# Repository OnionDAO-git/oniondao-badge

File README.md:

# OnionDAO Badge

An open-source, hacker-conference-style electronic badge built around the
**ESP32-S3-WROOM-1-N8R8** (8 MB flash + 8 MB Octal PSRAM), with swappable
RF / audio / storage modules, an e-paper
(or TFT) display socket, a secure element, an I²C IO expander for the button
matrix, and dual side-mounted expansion ports for hardware mods.

Designed in **KiCad 9.0.3**. The hardware (schematics, PCB, BOM, fabrication
outputs, STEP model) lives in [`pcb/`](pcb). The software lives in
[`software/`](software) and is community-driven — PRs welcome.

> **🧅 Just got a badge?** New attendees start with the
> **[Badge Quickstart](docs/BADGE-QUICKSTART.md)** — power it on, confirm Onion
> OS is running, and link it to your profile in ~5 minutes.

---

## Table of Contents

- [At a Glance](#at-a-glance)
- [Block Diagram](#block-diagram)
- [Repository Layout](#repository-layout)
- [Hardware Documentation](#hardware-documentation)
- [Quick Start (Software)](#quick-start-software)
- [Pinout Cheat Sheet](#pinout-cheat-sheet)
- [Contributing Software Mods & Guides](#contributing-software-mods--guides)
- [License](#license)

---

## At a Glance

| | |
|---|---|
| **MCU** | Espressif **ESP32-S3-WROOM-1-N8R8** (Wi-Fi + BT 5.0 LE, dual-core Xtensa LX7) |
| **Memory** | 8 MB quad-SPI flash (`N8`) + 8 MB **Octal-SPI (OPI)** PSRAM (`R8`) |
| **USB / Serial** | WCH **CH340C** USB-UART bridge w/ DTR/RTS auto-reset |
| **Secure Element** | Microchip **ATECC608B-SSHDA** (I²C, power-gated) |
| **IO Expander** | TI **TCA9534** (I²C, addr `0x20`) driving the 6-button matrix (PB1–PB6) |
| **Display** | 24-pin socket (`J4`) — E-Ink / TFT SPI with `BUSY`, `RST`, `DC`, `CS`, `SCK`, `MOSI` |
| **Audio (mod)** | NS4168 I²S amplifier + SPH0641 PDM mic (Sound Module) |
| **Sub-GHz (mod)** | TI **CC1101** SPI radio (315/433/868/915 MHz) |
| **Expansion** | Left port `J8` (10 pin) + Right port `J10` (10 pin) — VCC / GND + GPIO |
| **GPIO Used** | 28 of the available ESP32-S3 GPIOs |
| **Power Gate** | Q5 (SS8050) on `GPIO18` enables the peripheral `PWR` rail |

## Block Diagram

```
                              ┌────────────────────────┐
        USB-C ── CH340C ──────│ UART0  GPIO43/44       │
                              │                        │
   ┌── BOOT btn ── GPIO0 ─────│ STRAP                  │
   │                          │                        │
   │   ATECC608B ──┬─ SCL G9 ─│ I²C0                   │
   │   TCA9534  ──┘  SDA G10  │   ◄── INT G1 (PBINT)   │
   │                          │                        │
   │   J4 Display ─SPI──── G11/12/13/14/17/21          │
   │                          │                        │
   │   J8 Left   ── G48/47/19/42/41/40                  │  ESP32-S3-WROOM-1
   │   J10 Right ── G38/39/16/15/7/6/5/4                │
   │                          │                        │
   │   GPIO18 ──── Q5 ────────│ PWR rail to gated peripherals
   │   GPIO8  ──── SE_EN  ────│ ATECC608B power gate
   │                          └────────────────────────┘
   │
   └── PB1..PB6 ── TCA9534 P0..P5 ──► INT line ── GPIO1
```

## Repository Layout

```
oniondao-badge/
├── README.md                   ← you are here
├── pcb/                        ← KiCad 9.0.3 hardware sources
│   ├── oniondao-badge.kicad_pro
│   ├── oniondao-badge.kicad_sch         (top-level schematic)
│   ├── oniondao-badge.kicad_pcb         (board layout)
│   ├── CC1101_MOD.kicad_sch              (Sub-GHz RF module)
│   ├── SOUND_MOD.kicad_sch               (I²S amp + PDM mic)
│   ├── oniondao-badge.step              (full 3D model)
│   ├── 3d/                               (additional STEP assets)
│   ├── production/                       (gerbers, BOMs, netlist)
│   ├── oniondao-badge_top.png           (board render — top)
│   ├── oniondao-badge_btm.png           (board render — bottom)
│   └── oniondao badge.html                   (interactive IO reference)
├── docs/
│   ├── HARDWARE.md             ← deep dive on every subsystem
│   ├── PINOUT.md               ← full GPIO ↔ net ↔ peripheral table
│   ├── MODULES.md              ← swappable modules & their pinmaps
│   └── CONTRIBUTING.md         ← how to PR a mod / guide / example
└── software/
    ├── README.md
    ├── examples/               ← minimal, single-feature firmware
    ├── guides/                 ← end-to-end how-tos
    └── mods/                   ← community firmware mods & forks
```

> **Tip:** open [`pcb/oniondao badge.html`](pcb/oniondao%20badge.html) in a browser for
> a colour-coded, searchable, filterable view of the IO table. It is the
> source of truth that [`docs/PINOUT.md`](docs/PINOUT.md) mirrors in markdown.

## Hardware Documentation

The docs are split so you can read just what you need:

- **[docs/HARDWARE.md](docs/HARDWARE.md)** — overview of every subsystem on
  the board: power, USB/UART, boot circuit, I²C bus, display socket, secure
  element, button matrix, expansion ports.
- **[docs/PINOUT.md](docs/PINOUT.md)** — the complete GPIO map: every used
  pin, its net, direction, interface, and the peripheral it connects to.
- **[docs/MODULES.md](docs/MODULES.md)** — the swappable modules
  (CC1101 / Sound) and the shared-GPIO assignments. Read
  this **first** if you are writing firmware that touches the side ports.

### Manufacturing

- Gerbers, drill files, and pick-and-place are zipped in
  [`pcb/production/oniondao-badge.zip`](pcb/production/oniondao-badge.zip).
- BOMs per variant: `bom-list_cc1101.xlsx`, `bom-list_sound.xlsx`,
  `bom-list_lanyard_new.xlsx`.
- IPC-D-356 netlist: `pcb/production/netlist.ipc`.

## Quick Start (Software)

The badge enumerates as a standard CH340 serial port, so any ESP32-S3 toolchain
works at the hardware level — **ESP-IDF**, **Arduino-ESP32**, **PlatformIO**,
**MicroPython**, **CircuitPython**.

> **Building the firmware in this repo?** The projects under `software/` are
> **ESP-IDF v5.5.x** projects (with the Arduino core as a component). Follow the
> step-by-step **[VS Code + ESP-IDF setup guide](software/guides/esp-idf-vscode-setup.md)**
> to install the toolchain and flash a badge.

### Memory configuration (N8R8)

The populated module is an **ESP32-S3-WROOM-1-N8R8**: 8 MB flash + 8 MB PSRAM
in **Octal (OPI)** mode. PSRAM will not initialise unless you select Octal
mode explicitly — quad-mode defaults silently disable it. Set per toolchain:

| Toolchain | Flash | PSRAM |
|-----------|-------|-------|
| **ESP-IDF** (`sdkconfig`) | `CONFIG_ESPTOOLPY_FLASHSIZE_8MB=y` | `CONFIG_SPIRAM=y`, `CONFIG_SPIRAM_MODE_OCT=y`, `CONFIG_SPIRAM_SPEED_80M=y` |
| **Arduino-ESP32** (boards menu) | `Flash Size = 8MB` | `PSRAM = OPI PSRAM` |
| **PlatformIO** | `board_build.flash_size = 8MB` | `board_build.arduino.memory_type = qio_opi` + `-DBOARD_HAS_PSRAM` |

The firmware projects under [`software/`](software) already carry these settings
in their `sdkconfig.defaults` — see the
[VS Code + ESP-IDF setup guide](software/guides/esp-idf-vscode-setup.md).

### Programming

1. Plug in USB-C. The CH340C + DTR/RTS auto-reset circuit (Q1/Q2 on
   `GPIO0`/`EN`) means **you do not need to hold BOOT** — the toolchain
   strobes it for you.
2. If auto-reset ever fails: hold **BOOT** (the SW button tied to `GPIO0`),
   tap **RESET**, release **BOOT**, then flash.

### Minimal Arduino example

```cpp
// Blink the peripheral power rail and read the BOOT button.
#define PWR_EN   18    // Q5 base — enables peripheral VCC
#define BOOT_BTN 0     // strapping pin, doubles as user button after boot

void setup() {
  Serial.begin(115200);          // CH340C on UART0 (GPIO43/44)
  pinMode(PWR_EN, OUTPUT);
  pinMode(BOOT_BTN, INPUT_PULLUP);
  digitalWrite(PWR_EN, HIGH);    // power-up peripherals
}

void loop() {
  Serial.printf("BOOT btn: %d\n", digitalRead(BOOT_BTN));
  delay(250);
}
```

### Reading the 6 user buttons

The PB1–PB6 buttons are wired to the **TCA9534** IO expander (I²C
addr `0x20`), not directly to the ESP32. A button press pulls `PBINT`
(`GPIO1`) low; read the expander register over I²C to find which one.

```cpp
#include <Wire.h>
#define SCL_PIN 9
#define SDA_PIN 10
#define PBINT   1
#define TCA9534 0x20

void buttonISR();

void setup() {
  Wire.begin(SDA_PIN, SCL_PIN, 400000);   // I²C Fast Mode
  pinMode(PBINT, INPUT_PULLUP);
  attachInterrupt(PBINT, buttonISR, FALLING);
}

void buttonISR() {
  Wire.beginTransmission(TCA9534);
  Wire.write(0x00);                       // Input port register
  Wire.endTransmission(false);
  Wire.requestFrom(TCA9534, 1);
  uint8_t state = Wire.read();            // bit N low = PB(N+1) pressed
  // ... dispatch on `state`
}
```

See [`software/examples/`](software/examples) for working firmware
covering display, audio, RF, and the secure element.

## Pinout Cheat Sheet

Source of truth: [`pcb/oniondao badge.html`](pcb/oniondao%20badge.html) — open it in
a browser for the filterable view. The markdown mirror is
[`docs/PINOUT.md`](docs/PINOUT.md).

### Core / UART / Boot

| GPIO | Net | Dir | Peripheral | Notes |
|------|-----|-----|------------|-------|
| `GPIO0`  | `IO0` | IN  | BOOT button + auto-reset Q1/Q2 | **Strapping** — LOW at power-on → download mode |
| `GPIO43` | `TX0` | OUT | CH340C RXD (via R1 220Ω) | UART0 TX |
| `GPIO44` | `RX0` | IN  | CH340C TXD | UART0 RX |
| `GPIO18` | `PWR` | OUT | Q5 SS8050 → peripheral VCC | HIGH = enable power gate |

### I²C Bus (Security Chip + IO Expander)

| GPIO | Net | Dir | Peripheral | Notes |
|------|-----|-----|------------|-------|
| `GPIO9`  | `SCL`   | OUT | TCA9534 + ATECC608B    | 400 kHz max (Fast Mode) |
| `GPIO10` | `SDA`   | I/O | TCA9534 + ATECC608B    | TCA9534 @ `0x20` |
| `GPIO1`  | `PBINT` | IN  | TCA9534 INT → PB1..PB6 | Active LOW, `attachInterrupt(FALLING)` |
| `GPIO8`  | `SE_EN` | OUT | ATECC608B enable       | HIGH = active — power-gate when idle |

### Display Socket J4 (E-Ink / TFT SPI)

| GPIO | Net | Dir | J4 Pin | Function |
|------|-----|-----|--------|----------|
| `GPIO14` | `RS`   | OUT | 3  | Display RESET — LOW ≥10 ms during init |
| `GPIO13` | `DC`   | OUT | 11 | Data / Command select (HIGH = data) |
| `GPIO12` | `CS`   | OUT | 12 | SPI Chip Select (active LOW) |
| `GPIO11` | `SCK`  | OUT | 13 | SPI Clock |
| `GPIO21` | `BUSY` | IN  | 9  | Busy — wait LOW before next refresh |
| `GPIO17` | `SDI`  | OUT | 23 | SPI MOSI |

### Expansion Ports

| Pin | Left (J8) | Right (J10) |
|-----|-----------|-------------|
| 1   | GND       | GND |
| 2   | VCC       | VCC |
| 3   | `GPIO48`  | `GPIO38` |
| 4   | `GPIO47`  | `GPIO39` |
| 5   | `GPIO19`  | `GPIO16` |
| 6   | `GPIO42`  | `GPIO15` |
| 7   | `GPIO41`  | `GPIO7`  |
| 8   | `GPIO40`  | `GPIO6`  |
| 9   | VCC       | `GPIO5`  |
| 10  | GND       | `GPIO4`  |

> **Heads-up:** the **Sound Module** and **CC1101 Module** both reuse the
> same set of side-port GPIOs. Only one module's firmware can drive those
> pins at a time. See [`docs/MODULES.md`](docs/MODULES.md) for the exact
> overlap and how to choose at compile time.

## Contributing Software Mods & Guides

We want this badge to be a **playground**. If you wrote a synth, a CC1101
replay tool, an OLED demo, a CTF challenge, a CircuitPython port — open a PR
into [`software/`](software).

1. Pick the right folder:
   - `software/examples/` — one feature, minimal code, no story.
   - `software/guides/` — step-by-step tutorials (markdown + code).
   - `software/mods/` — full firmware projects / forks / variants.
2. Add a folder named after your mod, with a `README.md` describing what it
   does, which GPIOs / modules it requires, and how to build & flash.
3. Open a PR. Use the template in `.github/PULL_REQUEST_TEMPLATE.md`.

Full guidelines: [`docs/CONTRIBUTING.md`](docs/CONTRIBUTING.md).

## License

Hardware sources (KiCad files under `pcb/`) are released under
**CERN-OHL-S v2** unless a file header states otherwise. Software in
`software/` defaults to **MIT** — individual mods may override in their own
folder's `LICENSE` file.

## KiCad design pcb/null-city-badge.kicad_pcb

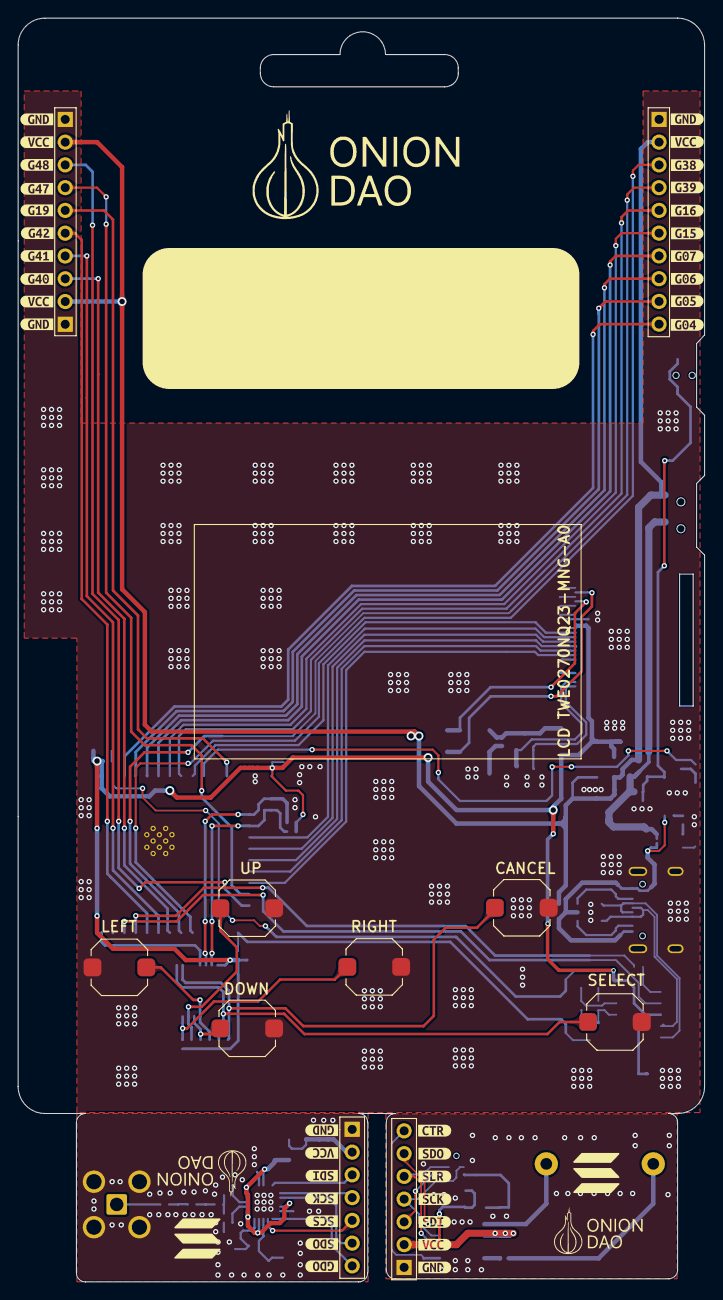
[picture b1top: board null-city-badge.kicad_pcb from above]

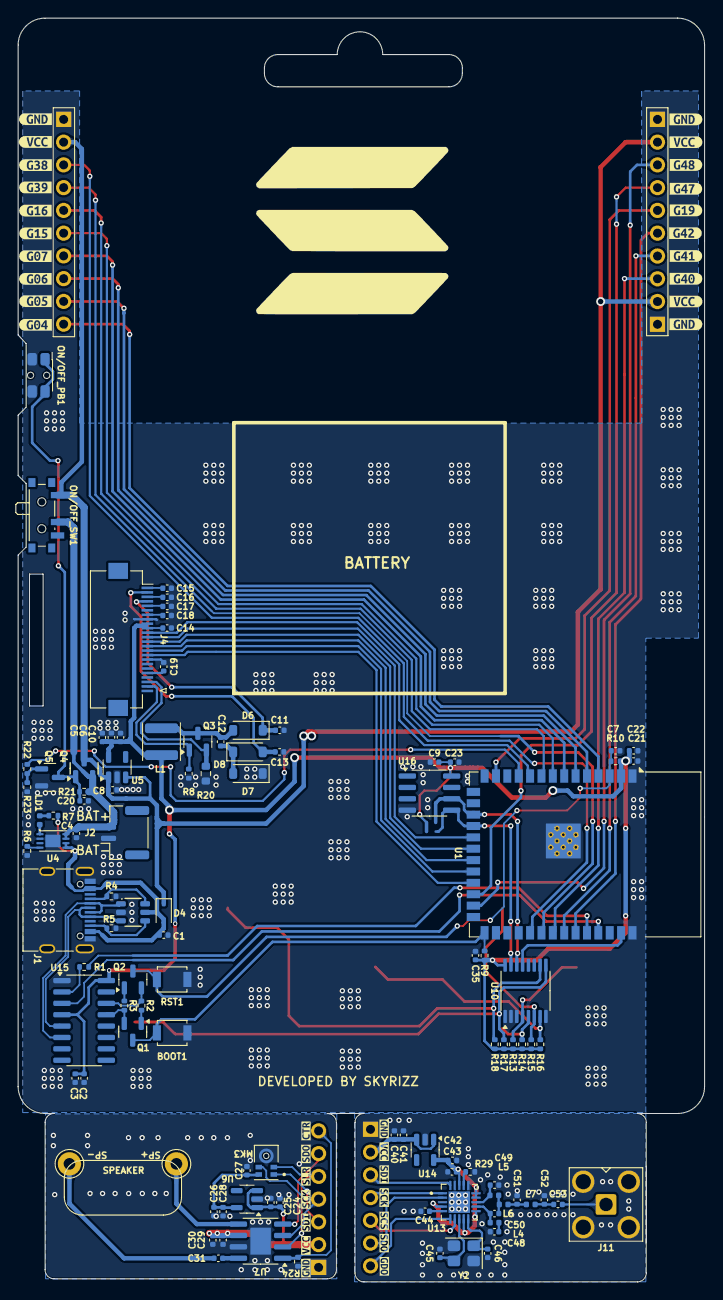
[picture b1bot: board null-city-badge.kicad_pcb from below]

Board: 2 copper layers, 76.6 x 141.1 mm, 184 parts (140 on the bottom side), 94 nets.

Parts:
BOOT1: SW_Push; SW_SPST_B3U-1000P
C1, C3, C6, C7, C9, C11, C12, C13, C14, C15, C16, C17, C18, C19: 1U; C_0402_1005Metric
C2, C10, C21, C23, C24, C27, C28, C35, C41, C43, C44: 100n; C_0402_1005Metric
C4, C5, C8, C25, C26, C30, C31, C40, C42: 10U; C_0402_1005Metric
C20, C22: 2U2; C_0402_1005Metric
C29: 22U; C_0402_1005Metric
C45, C46: 27p; C_0402_1005Metric
C48, C53: 220p; C_0402_1005Metric
C49, C50: 3.9p; C_0402_1005Metric
C51: 8.2p; C_0402_1005Metric
C52: 5.6p; C_0402_1005Metric
D1: SRV05-4-P-T7; SOT-23-6_L2.9-W1.6-P0.95-LS2.8-BR
D4: BAT60A; D_SOD-323
D6, D7, D8: MBR0540; D_SOD-123
J1: USB_C_Receptacle_USB2.0_16P; USB_C_Receptacle_G-Switch_GT-USB-7010ASV
J2: Conn_01x02_Pin; JST_GH_SM02B-GHS-TB_1x02-1MP_P1.25mm_Horizontal
J3: Conn_01x04_Pin; PinHeader_1x04_P2.54mm_Vertical
J4: Conn_01x24_Socket; Hirose_FH12-24S-0.5SH_1x24-1MP_P0.50mm_Horizontal
J6, J12: Conn_01x07_Pin; PinHeader_1x07_P2.54mm_Vertical
J8: Conn_01x06_Pin; PinHeader_1x06_P2.54mm_Vertical
J10: Conn_01x10_Pin; PinHeader_1x10_P2.54mm_Vertical
J11: Conn_Coaxial_Small; SMA_Amphenol_901-143_Horizontal
L1: 47UH; L_APV_ANR4020
L4: 22nH; L_0402_1005Metric
L5, L6, L7: 27nH; L_0402_1005Metric
LD1: LED; LED_0402_1005Metric
MK3: SPH0641LM4H-1; MIC_SPH0641LM4H-1
ON/OFF_PB1: SW_Push; SW_SPST_EVQP7C
ON/OFF_SW1: SW_SPDT; SW_SPDT_PCM12
PB1, PB2, PB3, PB4, PB5, PB6: SW_Push; SW_Push_1TS009xxxx-xxxx-xxxx_6x6x5mm
Q1, Q2, Q5: SS8050; SOT-23
Q3: IRLML0030; SOT-23
Q4: AO3401A; Q_SOT-23
R1: 220; R_0402_1005Metric
R2, R3, R6, R9, R10, R13, R14, R15, R16, R17, R18: 10K; R_0402_1005Metric
R4, R5: 5K1; R_0402_1005Metric
R7, R22, R24: 1K; R_0402_1005Metric
R8, R29: 56K; R_0402_1005Metric
R20: 2R2; R_0603_1608Metric
R21, R23: 22K; R_0402_1005Metric
RST1: SW_Push; SW_SPST_B3U-1000P
TP1: SP+; Pin_D1.3mm_L11.0mm
TP2: SP-; Pin_D1.3mm_L11.0mm
U1: ESP32-S3-WROOM-1
U4: MCP73831-2-MC; DFN-8-1EP_3x2mm_P0.5mm_EP1.7x1.4mm
U5, U6, U14: ME6211C33M5; SOT-23-5
U7: NS4168; SOIC-8-1EP_3.9x4.9mm_P1.27mm_EP2.29x3mm
U10: TCA9534; TSSOP-16_4.4x5mm_P0.65mm
U13: CC1101RGP; QFN50P400X400X100-21N
U15: CH340C; SOIC-16_3.9x9.9mm_P1.27mm
U16: ATECC608B-SSHDA; SOIC-8_3.9x4.9mm_P1.27mm
Y2: 26Mhz; Crystal_SMD_3225-4Pin_3.2x2.5mm
kibuzzard-69D7A2FA: G***; kibuzzard-69D7A2FA
kibuzzard-69D7A5EF: G***; kibuzzard-69D7A5EF
kibuzzard-69D7A5F4, kibuzzard-69D7A5F4#2: G***; kibuzzard-69D7A5F4
kibuzzard-69D7A28C, kibuzzard-69D7A28C#2: G***; kibuzzard-69D7A28C
kibuzzard-69D7A260, kibuzzard-69D7A260#2: G***; kibuzzard-69D7A260
kibuzzard-69D7A287, kibuzzard-69D7A287#2: G***; kibuzzard-69D7A287
kibuzzard-69D7A626, kibuzzard-69D7A626#2: G***; kibuzzard-69D7A626
kibuzzard-69D7A630, kibuzzard-69D7A630#2: G***; kibuzzard-69D7A630
kibuzzard-69D7A638, kibuzzard-69D7A638#2: G***; kibuzzard-69D7A638
kibuzzard-69D7A640, kibuzzard-69D7A640#2: G***; kibuzzard-69D7A640
kibuzzard-69D7D7AD: G***; kibuzzard-69D7D7AD
kibuzzard-69D7D7BC: G***; kibuzzard-69D7D7BC
kibuzzard-69D7D86C: G***; kibuzzard-69D7D86C
kibuzzard-69D7D873: G***; kibuzzard-69D7D873
kibuzzard-69D663AD: G***; kibuzzard-69D663AD
kibuzzard-69D663C6, kibuzzard-69D663C6#2, kibuzzard-69D663C6#3, kibuzzard-69D663C6#4, kibuzzard-69D663C6#5: G***; kibuzzard-69D663C6
kibuzzard-69D665BB: G***; kibuzzard-69D665BB
kibuzzard-69D665D2: G***; kibuzzard-69D665D2
kibuzzard-69D665E3: G***; kibuzzard-69D665E3
kibuzzard-69D665EF: G***; kibuzzard-69D665EF
kibuzzard-69D665FA: G***; kibuzzard-69D665FA
kibuzzard-69D673B2: G***; kibuzzard-69D673B2
kibuzzard-69D673C1: G***; kibuzzard-69D673C1
kibuzzard-69D673C9: G***; kibuzzard-69D673C9
kibuzzard-69D673D2: G***; kibuzzard-69D673D2
kibuzzard-69D6643F: G***; kibuzzard-69D6643F
kibuzzard-69D6645F: G***; kibuzzard-69D6645F
kibuzzard-69D7012B: G***; kibuzzard-69D7012B
kibuzzard-69D66402: G***; kibuzzard-69D66402
kibuzzard-69D66408: G***; kibuzzard-69D66408
kibuzzard-69D66453: G***; kibuzzard-69D66453
kibuzzard-69D66465: G***; kibuzzard-69D66465
kibuzzard-69D66565, kibuzzard-69D66565#2, kibuzzard-69D66565#3: G***; kibuzzard-69D66565
kibuzzard-69D66580, kibuzzard-69D66580#2, kibuzzard-69D66580#3: G***; kibuzzard-69D66580
kibuzzard-69D66624: G***; kibuzzard-69D66624
kibuzzard-69D70112, kibuzzard-69D70112#2, kibuzzard-69D70112#3: G***; kibuzzard-69D70112
kibuzzard-69D70126: G***; kibuzzard-69D70126
kibuzzard-69D70130: G***; kibuzzard-69D70130
kibuzzard-69D70134: G***; kibuzzard-69D70134
kibuzzard-69D70186: G***; kibuzzard-69D70186
kibuzzard-69E6D5DE: G***; kibuzzard-69E6D5DE
kibuzzard-69E6D5FA: G***; kibuzzard-69E6D5FA
kibuzzard-69E6D61C: G***; kibuzzard-69E6D61C
kibuzzard-69E6D63B: G***; kibuzzard-69E6D63B
kibuzzard-69E6D601: G***; kibuzzard-69E6D601
kibuzzard-69E6D610: G***; kibuzzard-69E6D610
kibuzzard-69E6D626: G***; kibuzzard-69E6D626
kibuzzard-69E6D641: G***; kibuzzard-69E6D641
kibuzzard-69E6DA12: G***; kibuzzard-69E6DA12
kibuzzard-69E6DA18: G***; kibuzzard-69E6DA18

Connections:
3V3: C2.1, C3.1, C5.1, C6.1, C9.1, C10.1, C14.2, C21.2, C22.2, C23.2, C35.2, J4.9, J4.10, L1.1, R9.2, R10.2, R13.2, R14.2, R15.2, R16.2, R17.2, R18.2, U1.2 (3V3), U5.5 (V_{OUT}), U10.16 (VDD), U15.4 (V3), U15.16 (VCC), U16.8 (VCC)
3V3_1: C26.1, C27.1, C28.2, MK3.5 (VDD), U6.5 (V_{OUT})
3V3_4: C42.1, C43.1, U13.4 (DVDD), U13.9 (AVDD_9), U13.11 (AVDD_11), U13.14 (AVDD_14), U13.15 (AVDD_15), U13.18 (DGUARD), U14.5 (V_{OUT})
/1CS: J3.3, U1.33 (IO40)
/1SCK: J10.4, U1.32 (IO39)
/1SDI: J10.3, U1.31 (IO38)
/1SDO: J3.4, U1.34 (IO41)
/2CS: J8.5, U1.13 (USB_D-)
/2SCK: J8.4, U1.24 (IO47)
/2SDI: J8.3, U1.25 (IO48)
/2SDO: J8.6, U1.35 (IO42)
/3CS: J10.9, U1.5 (IO5)
/3SCK: J10.8, U1.6 (IO6)
/3SDI: J10.7, U1.7 (IO7)
/3SDO: J10.10, U1.4 (IO4)
/BUSY: J4.16, U1.23 (IO21)
/CC1: D1.6 (I/O), J1.A5 (CC1), R4.1
/CC2: D1.4 (I/O), J1.B5 (CC2), R5.1
/CC1101 MODULE/CS_4: J12.5, U13.7 (CSN)
/CC1101 MODULE/GDO: J12.7, U13.6 (GDO(ATEST))
/CC1101 MODULE/SCK_4: J12.4, U13.1 (SCLK)
/CC1101 MODULE/SDI_4: J12.3, U13.20 (SI)
/CC1101 MODULE/SDO_4: J12.6, U13.2 (SO(GDO1))
/CS: J4.13, U1.20 (IO12)
/CS1: J10.5, U1.9 (IO16)
/D+: D1.3 (I/O), J1.A6 (D+), J1.B6 (D+), U15.5 (UD+)
/D-: D1.1 (I/O), J1.A7 (D-), J1.B7 (D-), U15.6 (UD-)
/DC: J4.14, U1.21 (IO13)
/DTR: Q1.2 (E), R3.1, U15.13 (~DTR)
/EN: C7.1, Q2.3 (C), R10.1, RST1.2, U1.3 (EN)
/GDR: J4.23, Q3.1 (G), R8.2
/IO0: BOOT1.2, Q1.3 (C), R9.1, U1.27 (IO0)
/PB1: PB1.2, R13.1, U10.4 (P0)
/PB2: PB2.2, R14.1, U10.5 (P1)
/PB3: PB3.2, R15.1, U10.6 (P2)
/PB4: PB4.2, R16.1, U10.7 (P3)
/PB5: PB5.2, R17.1, U10.9 (P4)
/PB6: PB6.2, R18.1, U10.10 (P5)
/PBINT: U1.39 (IO1), U10.13 (~INT)
/PWR: R22.1, U1.11 (IO18)
/RESE: J4.22, Q3.2 (S), R20.2
/RS: J4.15, U1.22 (IO14)
/RTS: Q2.2 (E), R2.1, U15.14 (~RTS)
/RX0: R1.2, U1.36 (RXD0)
/SCK: J4.12, U1.19 (IO11)
/SCL: U1.17 (IO9), U10.14 (SCL), U16.6 (SCL)
/SDA: U1.18 (IO10), U10.15 (SDA), U16.5 (SDA)
/SDI: J4.11, U1.10 (IO17)
/SDO: J10.6, U1.8 (IO15)
/SOUND MODULE/CTRL: J6.7, R24.1, U7.1 (CTRL)
/SOUND MODULE/SCK_1: J6.4, MK3.4 (CLOCK), U7.3 (BCLK)
/SOUND MODULE/SDI_1: J6.3, MK3.1 (DATA)
/SOUND MODULE/SDO_1: J6.6, U7.4 (SD)
/SOUND MODULE/WS_1: J6.5, MK3.2 (SELECT), U7.2 (L/RCLK)
/STAT: LD1.1 (K), U4.5 (STAT)
/TX0: U1.37 (TXD0), U15.3 (RXD)
/VGH: C11.1, D6.1 (K), J4.4
/VGL: C13.2, D8.2 (A), J4.2
BAT: C4.1, J2.2, ON/OFF_SW1.2 (B), Q4.2 (S), R21.2, U4.3 (V_{BAT}), U4.4 (V_{BAT})
GND1: BOOT1.1, C1.2, C2.2, C3.2, C4.2, C5.2, C6.2, C7.2, C8.2, C9.2, C10.2, C11.2, C13.1, C14.1, C15.1, C16.1, C17.1, C18.1, C19.1, C20.2, C21.1, C22.1, C23.1, C35.1, D1.2 (VN), D7.1 (K), J1.A1 (GND), J1.A12 (GND), J1.B1 (GND), J1.B12 (GND), J1.S1 (SHIELD), J2.1, J3.1, J4.8, J4.17, J8.1, J10.1, ON/OFF_PB1.2, PB1.1, PB2.1, PB3.1, PB4.1, PB5.1, PB6.1, Q5.2 (E), R4.2, R5.2, R6.1, R8.1, R20.1, R23.2, RST1.1, U1.1 (GND), U1.40 (GND), U1.41 (GND), U4.6 (V_{SS}), U4.9 (EP), U5.2 (V_{SS}), U10.1 (A0), U10.2 (A1), U10.3 (A2), U10.8 (GND), U15.1 (GND), U16.4 (GND)
GND_1: C24.2, C25.2, C26.2, C27.2, C28.1, C29.2, C30.2, J6.1, MK3.3_1 (GND), MK3.3_2 (GND), R24.2, U6.2 (V_{SS}), U7.7 (GND), U7.9 (GND)
GND_4: C40.2, C41.2, C42.2, C43.2, C44.1, C45.2, C46.2, C48.2, C49.1, C51.2, C52.1, J11.2 (Ext), J12.1, R29.1, U13.16 (GND_16), U13.19 (GND_19), U13.21 (EXP), U14.2 (V_{SS}), Y2.2, Y2.4
unnamed: C31.1, TP1.1
unnamed: C48.1, L4.2
unnamed: C50.1, L5.2, L6.1
unnamed: C51.1, L6.2, L7.1
unnamed: C52.2, C53.1, L7.2
unnamed: C12.1, D6.2 (A), L1.2, Q3.3 (D)
unnamed: C12.2, D7.2 (A), D8.1 (K)
unnamed: C15.2, J4.1
unnamed: C16.2, J4.3
unnamed: C17.2, J4.5
unnamed: C18.2, J4.7
unnamed: C19.2, J4.20
unnamed: C53.2, J11.1 (In)
unnamed: LD1.2 (A), R7.1
unnamed: Q1.1 (B), R2.2
unnamed: Q2.1 (B), R3.2
unnamed: C20.1, ON/OFF_PB1.1, Q4.1 (G), Q5.3 (C), R21.1
unnamed: Q5.1 (B), R22.2, R23.1
unnamed: R6.2, U4.8 (PROG)
unnamed: TP2.1, U7.5 (VON)
unnamed: C31.2, U7.8 (VOP)
unnamed: C44.2, U13.5 (DCOUPL)
unnamed: R29.2, U13.17 (RBIAS)
unnamed: C49.2, L5.1, U13.13 (RF_N)
unnamed: C50.2, L4.1, U13.12 (RF_P)
unnamed: C45.1, U13.8 (XOSC_Q1), Y2.3
unnamed: C46.1, U13.10 (XOSC_Q2), Y2.1
unnamed: R1.1, U15.2 (TXD)
VBUS: C1.1, D1.5 (VP), D4.2 (A), J1.A4 (VBUS), J1.A9 (VBUS), J1.B4 (VBUS), J1.B9 (VBUS), R7.2, U4.1 (V_{DD}), U4.2 (V_{DD})
VSYS: C8.1, D4.1 (K), J3.2, J8.2, J10.2, ON/OFF_SW1.1 (A), Q4.3 (D), U5.1 (V_{IN}), U5.3 (CE)
VSYS_1: C24.1, C25.1, C29.1, C30.1, J6.2, U6.1 (V_{IN}), U6.3 (CE), U7.6 (VDD)
VSYS_4: C40.1, C41.1, J12.2, U14.1 (V_{IN}), U14.3 (CE)

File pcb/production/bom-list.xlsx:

Designator | Footprint | Quantity | Value | LCSC Part # | Model number | Manufacturer
BOOT1, RST1 | SW_SPST_B3U-1000P | 2 | SW_Push |  | HX-B3U-1000P-1.6N | hanxia
C1, C11, C12, C13, C14, C15, C16, C17, C18, C19, C3, C6, C7, C9 | 0402 | 14 | 1U |  | CL05A105KP5NNNC | SAMSUNG
C10, C2, C21, C23, C24, C27, C28, C35, C41, C43, C44 | 0402 | 11 | 100n |  | CL05B104KO5NNNC | SAMSUNG
C20, C22 | 0402 | 2 | 2U2 |  | CL05A225MQ5NSNC | SAMSUNG
C25, C26, C30, C4, C40, C42, C5, C8 | 0402 | 8 | 10U |  | CL05A106MQ5NUNC | SAMSUNG
C29 | 0402 | 1 | 22U |  | GRM155R60J226ME11D | muRata
C45, C46 | 0402 | 2 | 27p |  | CC0402FRNPO9BN270 | YAGEO
C48, C53 | 0402 | 2 | 220p |  | CC0402KRX7R9BB221 | YAGEO
C49, C50 | 0402 | 2 | 3.9p |  | CC0402CRNPO9BN3R9 | YAGEO
C51 | 0402 | 1 | 8.2p |  | 0402CG8R2C500NT | FH
C52 | 0402 | 1 | 5.6p |  | 0402CG5R6C500NT | FH
D1 | SOT-23-6_L2.9-W1.6-P0.95-LS2.8-BR | 1 | SRV05-4-P-T7 | C85364 | SRV05-4-P-T7 | PROTEK
D4 | D_SOD-323 | 1 | BAT60A |  | BAT60A | Slkor
D6, D7, D8 | D_SOD-123 | 3 | MBR0540 |  | MBR0540 | CJ
J1 | USB_C_Receptacle_G-Switch_GT-USB-7010ASV | 1 | USB_C_Receptacle_USB2.0_16P |  | GT-USB-7010ASV | G-Switch
J10 | PinHeader_1x10_P2.54mm_Vertical | 1 | Conn_01x10_Pin |  | PZ254V-11-10P | XFCN
J11 | SMA_Amphenol_901-143_Horizontal | 1 | Conn_Coaxial_Small |  | 901-143 | Made in China
J12 | PinHeader_1x07_P2.54mm_Vertical | 1 | Conn_01x07_Pin |  | PZ254V-11-07P | XFCN
J2 | S2B-PH-SM4-TB | 1 | Conn_01x02_Pin |  | S2B-PH-SM4-TB | JST
J3, J6, J8 | PinHeader_1x06_P2.54mm_Vertical | 3 | Conn_01x06_Pin |  | PZ254V-11-06P | XFCN
J4 | Hirose_FH12-24S-0.5SH_1x24-1MP_P0.50mm_Horizontal | 1 | Conn_01x24_Socket |  | FH12-24S-0.5SH(55) | HRS
L1 | L_APV_ANR4020 | 1 | 47UH |  | FHD4020S-470MT | cjiang
L4 | 0402 | 1 | 22nH |  | LQG15HS22NJ02D | muRata
L5, L6, L7 | 0402 | 3 | 27nH |  | SDCL1005C27NJTDF | Sunlord
LD1 | 0402 | 1 | LED |  | Red
MK3 | InvenSense_ICS-43434-6_3.5x2.65mm | 1 | SPH0641LM4H-1 |  | SPH0641LM4H-1 | Knowles
ON/OFF_PB1 | SW_SPST_EVQP7C | 1 | SW_Push |  | EVQP7C01P | PANASONIC
ON/OFF_SW1 | SW_SPDT_PCM12 | 1 | SW_SPDT |  | SS-203-AGS7P-200 | XUNPU
PB1, PB2, PB3, PB4, PB5, PB6 | SW_SPST_B3SL-1002P | 6 | SW_Push |  | TL9210AF180Q
Q1, Q2, Q5 | SOT-23 | 3 | SS8050 |  | SS8050 | CJ
Q3 | SOT-23 | 1 | IRLML0030 |  | IRLML0030 | Hottech
Q4 | Q_SOT-23 | 1 | AO3401A | C15127 | AO3401A | AOS
R1 | 0402 | 1 | 220 |  | 0402WGF2200TCE | UNI-ROYAL
R10, R13, R14, R15, R16, R17, R18, R19, R2, R3, R6, R8, R9 | 0402 | 13 | 10K |  | RC0402FR-0710KL | YAGEO
R11, R12 | 0402 | 2 | 2K2 |  | 0402WGF2201TCE | UNI-ROYAL
R20 | 0603 | 1 | 2R2 |  | 0402WGF220KTCE | UNI-ROYAL
R21, R23 | 0402 | 2 | 22K |  | 0402WGF2202TCE | UNI-ROYAL
R22, R24, R7 | 0402 | 3 | 1K |  | 0402WGF1001TCE | UNI-ROYAL
R29 | 0402 | 1 | 56K |  | 0402WGF5602TCE | UNI-ROYAL
R4, R5 | 0402 | 2 | 5K1 |  | 0402WGF5101TCE | UNI-ROYAL
TP1 | Pin_D1.3mm_L11.0mm | 1 | SP+
TP2 | Pin_D1.3mm_L11.0mm | 1 | SP-
U1 | ESP32-S3-WROOM-1 | 1 | ESP32-S3-WROOM-1 |  | ESP32-S3-WROOM-1-N8R8 | ESPRESSIF
U10 | TSSOP-16_4.4x5mm_P0.65mm | 1 | TCA9534 |  | TCA9534PWR | TI
U14, U5, U6 | SOT-23-5 | 3 | ME6211C33M5 |  | ME6211C33M5G-N | MICRONE(
U13 | QFN50P400X400X100-21N | 1 | CC1101RGP |  | CC1101RGPR | TI
U2 | QFN-28-1EP_5x5mm_P0.5mm_EP3.35x3.35mm | 1 | CP2102N-Axx-xQFN28 |  | CP2102N-A02-GQFN28R | SKYWORKS/SILICON LABS
U3 | QFN40P300X300X33-21N | 1 | SE050C2HQ1_Z01SDZ |  | SE050C2HQ1/Z01SDZ | NXP
U4 | DFN-8-1EP_3x2mm_P0.5mm_EP1.7x1.4mm | 1 | MCP73831-2-MC |  | MCP73831T-2ACI/MC | MICROCHIP
U7 | SOIC-8-1EP_3.9x4.9mm_P1.27mm_EP2.29x3mm | 1 | NS4168 |  | NS4168 | Nsiway
Y2 | Crystal_SMD_3225-4Pin_3.2x2.5mm | 1 | 26Mhz |  | XL2EL89COI-111YLC-26M | YXC
LCD |  | 1 | 2.7in |  | YRD0270BBS800F7
Speaker |  | 1 | 8ohm 1w |  | 1609
Antenna |  | 1 | right angle antenna |  | 433mhz
Battery |  | 1 | 50x30
 | pcb |  | FR-4 board, double-sided, 1.6mm thickness, green solder mask with white text, 1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
 | SMT Stenci

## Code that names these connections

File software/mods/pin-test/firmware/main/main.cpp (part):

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
// CC1101 wiring on J8 (per the CC1101->J8 jumper mapping)
static const uint8_t CC1101_SCK = 47;
static const uint8_t CC1101_MISO = 42; // module SDO
static const uint8_t CC1101_MOSI = 48; // module SDI
static const uint8_t CC1101_CS = 19;   // module SCS
static const uint8_t CC1101_GDO0 = 41; // module GDO

static SPIClass cc1101SPI(FSPI);

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static const uint8_t SOUND_CTRL = 7;   // module CTR — NS4168 mode/shutdown
static const uint8_t SOUND_BCLK = 39;  // module SCK
static const uint8_t SOUND_WS = 16;    // module SLR (word select / LRCK)
static const uint8_t SOUND_DOUT = 15;  // module SDO -> NS4168 SD (data in to amp)

static i2s_chan_handle_t gSoundTxChan = NULL;

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// J8 (left port): GND VCC G48 G47 G19 G42 G41 G40 VCC GND
// J10 (top/right header): GND VCC G38 G39 G16 G15 G07 G06 G05 G04
static const TestPin kPins[] = {
  {48, "G48 (J8 pin 3 / CC1101 SDI)"},
  {47, "G47 (J8 pin 4 / CC1101 SCK)"},
  {19, "G19 (J8 pin 5 / CC1101 SCS)"},
  {42, "G42 (J8 pin 6 / CC1101 SDO)"},
  {41, "G41 (J8 pin 7 / CC1101 GDO)"},
  {40, "G40 (J8 pin 8, spare)"},
  {38, "G38 (J10 pin 3 / Sound SDI)"},
  {39, "G39 (J10 pin 4 / Sound SCK)"},
  {16, "G16 (J10 pin 5 / Sound SLR)"},
  {15, "G15 (J10 pin 6 / Sound SDO)"},
  {7,  "G07 (J10 pin 7 / Sound CTR)"},
  {6,  "G06 (J10 pin 8, spare)"},
  {5,  "G05 (J10 pin 9, spare)"},
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
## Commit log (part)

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2026-04-13 feat: main board with sub ghz and audio modules, remove lora and sdcard
2026-05-12 feat: final file for production with panel adjustment
2026-06-15 Update macOS ESP-IDF prereqs installation command in vscode extension setup
    Added 'dfu-util' and 'cmake' to the installation command for macOS. Otherwise installing EIM fails saying these are missing. Official docs are here: https://docs.espressif.com/projects/esp-idf/en/lat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
2026-06-16 Add Onion Bookshelf: a .txt book reader for the badge
    A self-contained Onion OS Lua app: main menu (Library/About/Help), a
    multi-book library, paged reading with per-book NVS bookmarks, and a
    verse-aware, panel-tuned layout (23 chars x 11 lines). Books are authored
    as plain books/*.txt and folded into an installable onion-bookshelf.lua by
    build.py (Python 3 stdlib) -- no EPUB, no firmware build. Ships a curated
    onion-themed shelf incl. an original fable. Installs via the Update Scripts
2026-06-18 Onion Bookshelf v0.3: version marker + roadmap/PR#5 notes
    - Add VERSION (0.3), shown on the About screen.
    - Bake a ROADMAP and quindelin's epub-reader (#5) handoff notes into the
    script header so they travel with every download (pre-baked pages = O(1)
    chapter jumps; SPIFFS budgeting is the real limit; refresh feel; ASCII-only
    font caveats).
2026-06-18 docs: add attendee Badge Quickstart + link from README
    A reader-goal 'just got a badge' tutorial: power on (battery/USB), confirm
    Onion OS is running (flash if not), connect, and link at /portal/onions —
    the step that isn't documented anywhere else. Fills the onboarding/tutorial
    gap (the steps existed only in a per-example README + a developer API doc).
2026-06-19 fix: monitoring with lower baud rate and fix full flash with spiffs
    Monitoring with a high baud rate equal to the one used for flashing creates reading issues so I defaulted to 115200 which is the default in the monitor-serial.sh script
    Fix the issue where doing a full flash with monitor would NOT flash the spiffs partition because after the initial flash the monitor mode was on and does not exit until user manually interrupts it.
2026-06-19 feat: add About page with personal profile gist (and test)
2026-06-19 feat: build flash script now supports flashing lua scripts
2026-06-19 chore: move feat out of main.cpp
